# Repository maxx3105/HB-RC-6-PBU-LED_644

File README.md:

# HB-RC-6-PBU-LED_644
6-Fach Wandtaster mit Signal-Led auf Basis der AskSin++ für Homematic

Dieses Projekt basiert auf der Arbeit von [pa-pa](https://github.com/pa-pa/AskSinPP) ,[Jérôme](https://github.com/jp112sdl/Beispiel_AskSinPP).

# Hardware

### Bauteile

Bauteile                   | Bezeichnung          | Anzahl | Kommentar   | 
-------------------------- | -------------------- | ------ | ----------- | 
R1,R2                      | 240 Ohm              |   2    |             |
R3,R4                      | 10K Ohm              |   2    |             |
R5                         | 1K  Ohm              |   1    |             |
R6                         | 100K Ohm             |   1    |             |
C1, ..., C10               | 100n                 |   10   |             |
SW1, ..., SW7              | Taster               |   7    |             |
U1                         | Atmega 644P-AU       |   1    |             |
U2                         | CC1101               |   1    |             |
U3                         | SN74LVC1T45DBV       |   1    |             |
Q1                         | IRLML9301            |   1    |             |
D1                         | SMD Led 0805 Rot     |   1    |             |
D2                         | SMD Led 0805 Grün    |   1    |             |
D3,...,D8                  | SK6812 Mini          |   6    |             |
D9,...,D14                 | WS2812-2020          |   6    | Alternative |

Reichelt Liste comeing soon

#### Sonstiges

CC1101 https://de.aliexpress.com/item/32924239954.html

Taster https://de.aliexpress.com/item/32660690016.html?spm=a2g0s.9042311.0.0.27424c4dqj9wVN

~8,3 cm Draht als Antenne

### Programmieradapter

- 1x FTDI Programmer https://www.az-delivery.de/products/ftdi-adapter-ft232rl
- 1x ISP Programmer https://www.diamex.de/dxshop/USB-ISP-Programmer-fuer-Atmel-AVR

# Software

https://www.arduino.cc/en/software

### Firmware

Sketch https://github.com/jp112sdl/HB-RC-6-PBU-LED/blob/master/HB-RC-6-PBU-LED.ino

# Bauanleitung

coming soon

# Bilder

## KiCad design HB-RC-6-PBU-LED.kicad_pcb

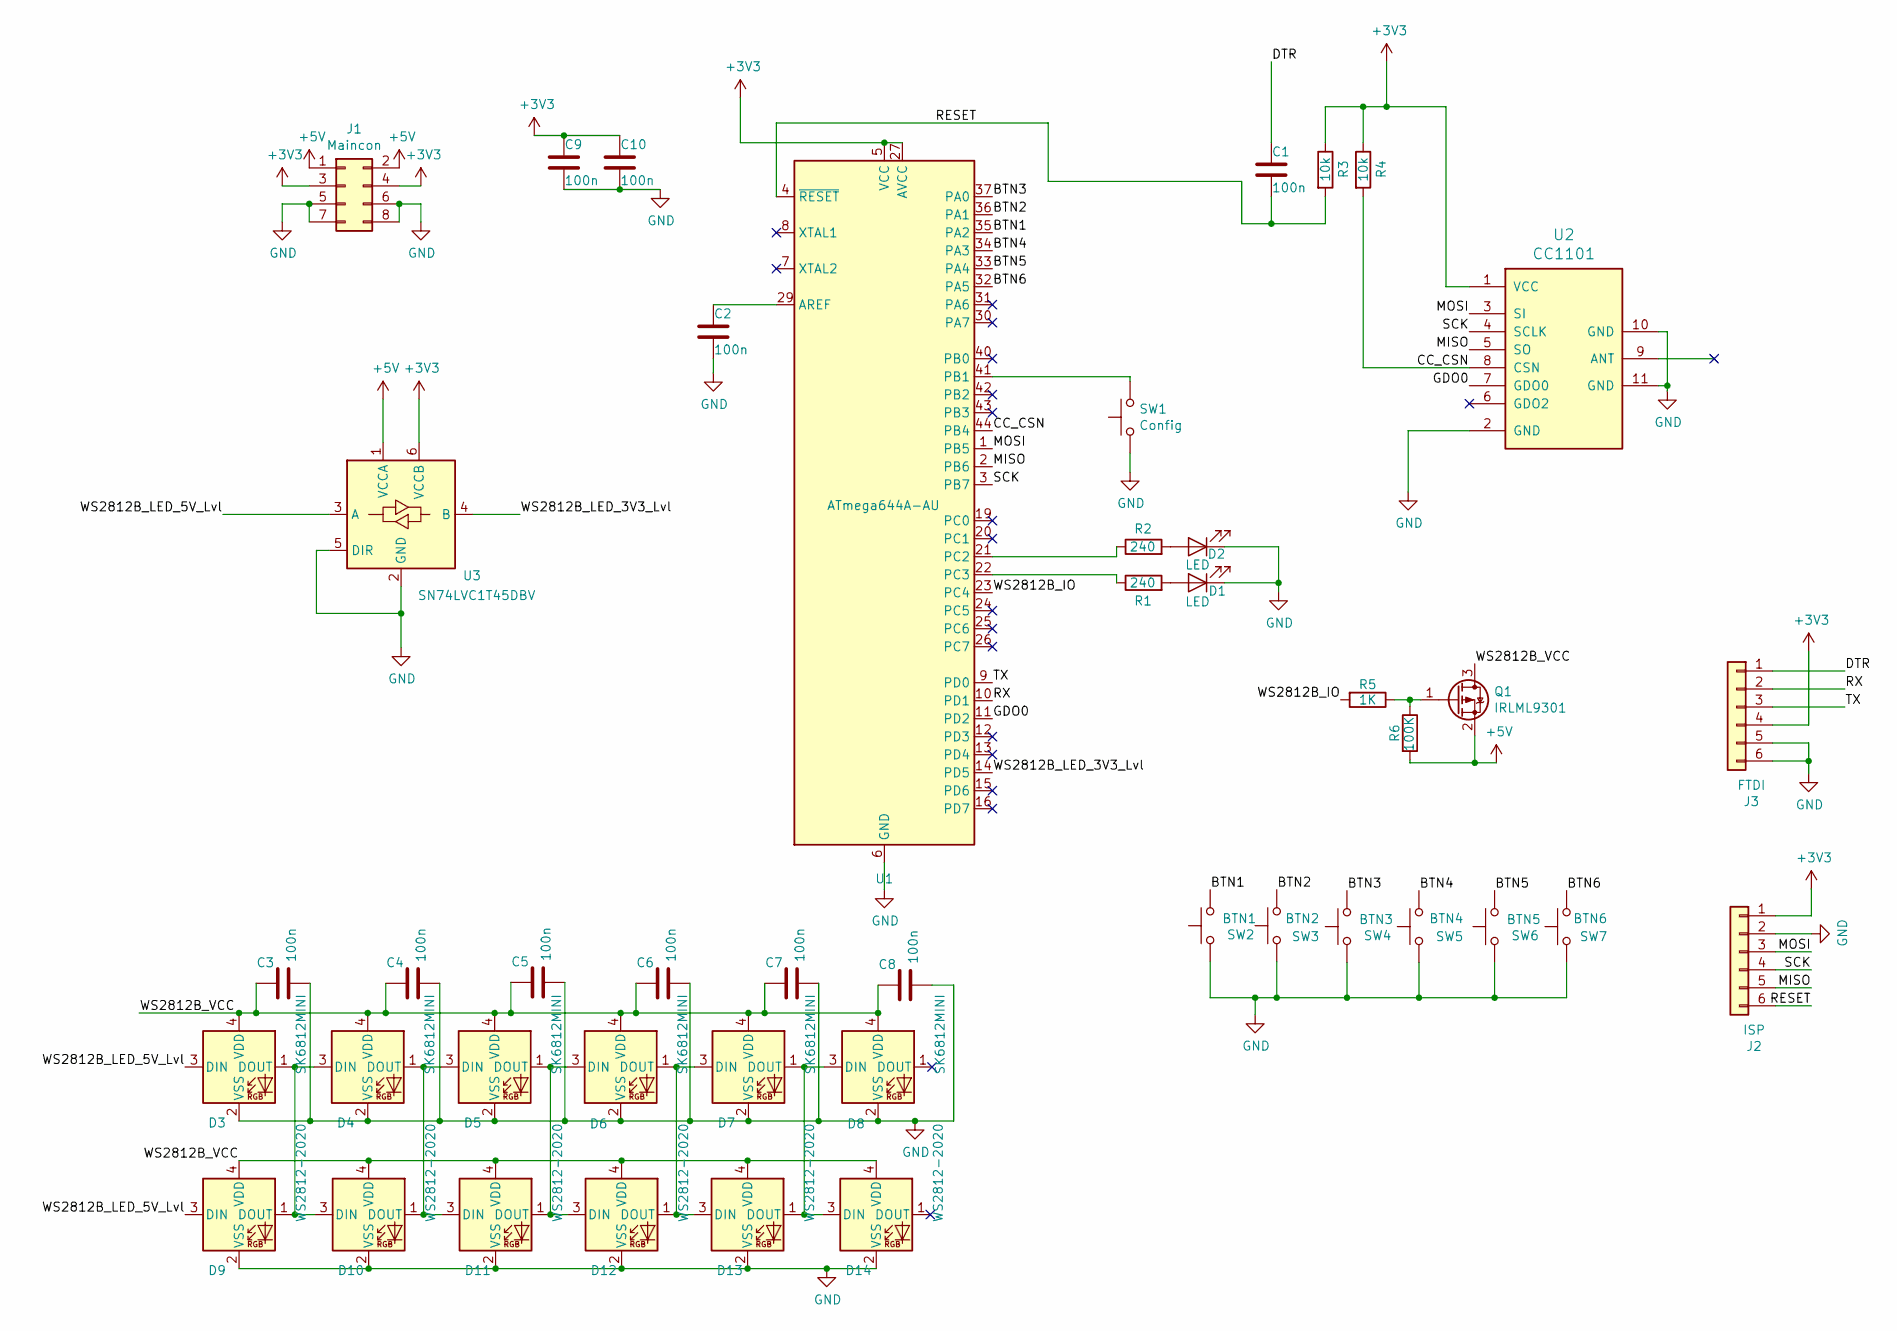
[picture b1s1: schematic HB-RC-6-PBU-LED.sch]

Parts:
C1, C2, C3, C4, C5, C6, C7, C8, C9, C10: 100n; C_0805_2012Metric_Pad1.18x1.45mm_HandSolder
D1, D2: LED; LED_0805_2012Metric_Pad1.15x1.40mm_HandSolder
D3, D4, D5, D6, D7, D8: SK6812MINI; LED_SK6812MINI_PLCC4_3.5x3.5mm_P1.75mm
D9, D10, D11, D12, D13, D14: WS2812-2020; LED_WS2812-2020
J1: Maincon; PinHeader_2x04_P2.54mm_Vertical_SMD
J2: ISP; PinHeader_1x06_P2.54mm_Vertical
J3: FTDI; PinHeader_1x06_P2.54mm_Vertical
Q1: IRLML9301; SOT-23
R1, R2: 240; R_0805_2012Metric_Pad1.20x1.40mm_HandSolder
R3, R4: 10k; R_0805_2012Metric_Pad1.20x1.40mm_HandSolder
R5: 1K; R_0805_2012Metric_Pad1.20x1.40mm_HandSolder
R6: 100K; R_0805_2012Metric_Pad1.20x1.40mm_HandSolder
SW1: Config; SW_SPST_FSMSM
SW2: BTN1; SW_SPST_FSMSM
SW3: BTN2; SW_SPST_FSMSM
SW4: BTN3; SW_SPST_FSMSM
SW5: BTN4; SW_SPST_FSMSM
SW6: BTN5; SW_SPST_FSMSM
SW7: BTN6; SW_SPST_FSMSM
U1: ATmega644A-AU; TQFP-44_10x10mm_P0.8mm
U2: CC1101; CC1101_SMD_THT
U3: SN74LVC1T45DBV; SOT-23-6

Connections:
+3V3: C9.1, C10.1, J1.3, J1.4, J2.1, J3.4, R3.1, R4.1, U1.5 (VCC), U1.17 (VCC), U1.27 (AVCC), U1.38 (VCC), U2.1 (VCC), U3.6 (VCCB)
+5V: J1.1, J1.2, Q1.2 (S), R6.2, U3.1 (VCCA)
/BTN1: SW2.2, U1.35 (PA2)
/BTN2: SW3.2, U1.36 (PA1)
/BTN3: SW4.2, U1.37 (PA0)
/BTN4: SW5.2, U1.34 (PA3)
/BTN5: SW6.2, U1.33 (PA4)
/BTN6: SW7.2, U1.32 (PA5)
/CC_CSN: R4.2, U1.44 (PB4), U2.8 (CSN)
/DTR: C1.1, J3.1
/GDO0: U1.11 (PD2), U2.7 (GDO0)
/MISO: J2.5, U1.2 (PB6), U2.5 (SO)
/MOSI: J2.3, U1.1 (PB5), U2.3 (SI)
/RESET: C1.2, J2.6, R3.2, U1.4 (~RESET)
/RX: J3.2, U1.10 (PD1)
/SCK: J2.4, U1.3 (PB7), U2.4 (SCLK)
/TX: J3.3, U1.9 (PD0)
/WS2812B_IO: R5.2, U1.23 (PC4)
/WS2812B_LED_3V3_Lvl: U1.14 (PD5), U3.4 (B)
/WS2812B_LED_5V_Lvl: D3.3 (DIN), D9.3 (DIN), U3.3 (A)
/WS2812B_VCC: C3.2, C4.2, C5.2, C6.2, C7.2, C8.2, D3.4 (VDD), D4.4 (VDD), D5.4 (VDD), D6.4 (VDD), D7.4 (VDD), D8.4 (VDD), D9.4 (VDD), D10.4 (VDD), D11.4 (VDD), D12.4 (VDD), D13.4 (VDD), D14.4 (VDD), Q1.3 (D)
GND: C2.2, C3.1, C4.1, C5.1, C6.1, C7.1, C8.1, C9.2, C10.2, D1.1 (K), D2.1 (K), D3.2 (VSS), D4.2 (VSS), D5.2 (VSS), D6.2 (VSS), D7.2 (VSS), D8.2 (VSS), D9.2 (VSS), D10.2 (VSS), D11.2 (VSS), D12.2 (VSS), D13.2 (VSS), D14.2 (VSS), J1.5, J1.6, J1.7, J1.8, J2.2, J3.5, J3.6, SW1.1, SW2.1, SW3.1, SW4.1, SW5.1, SW6.1, SW7.1, U1.6 (GND), U1.18 (GND), U1.28 (GND), U1.39 (GND), U2.2 (GND), U2.10 (GND), U2.11 (GND), U3.2 (GND), U3.5 (DIR)
unnamed: C2.1, U1.29 (AREF)
unnamed: D1.2 (A), R1.2
unnamed: D2.2 (A), R2.2
unnamed: D4.1 (DOUT), D5.3 (DIN), D10.1 (DOUT), D11.3 (DIN)
unnamed: D3.1 (DOUT), D4.3 (DIN), D9.1 (DOUT), D10.3 (DIN)
unnamed: D5.1 (DOUT), D6.3 (DIN), D11.1 (DOUT), D12.3 (DIN)
unnamed: D6.1 (DOUT), D7.3 (DIN), D12.1 (DOUT), D13.3 (DIN)
unnamed: D7.1 (DOUT), D8.3 (DIN), D13.1 (DOUT), D14.3 (DIN)
unnamed: Q1.1 (G), R5.1, R6.1
unnamed: R1.1, U1.22 (PC3)
unnamed: R2.1, U1.21 (PC2)
unnamed: SW1.2, U1.41 (PB1)

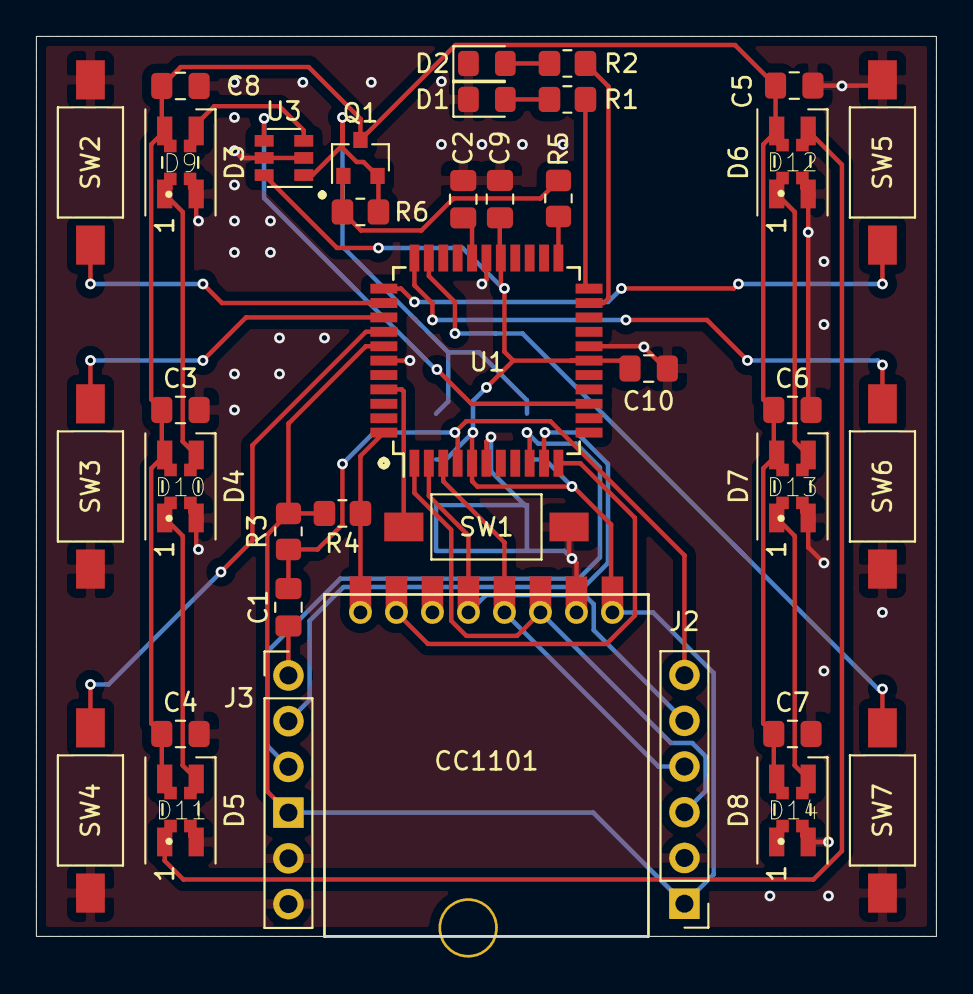
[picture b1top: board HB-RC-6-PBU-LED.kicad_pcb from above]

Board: 2 copper layers, 50.0 x 50.0 mm, 44 parts (1 on the bottom side), 34 nets.

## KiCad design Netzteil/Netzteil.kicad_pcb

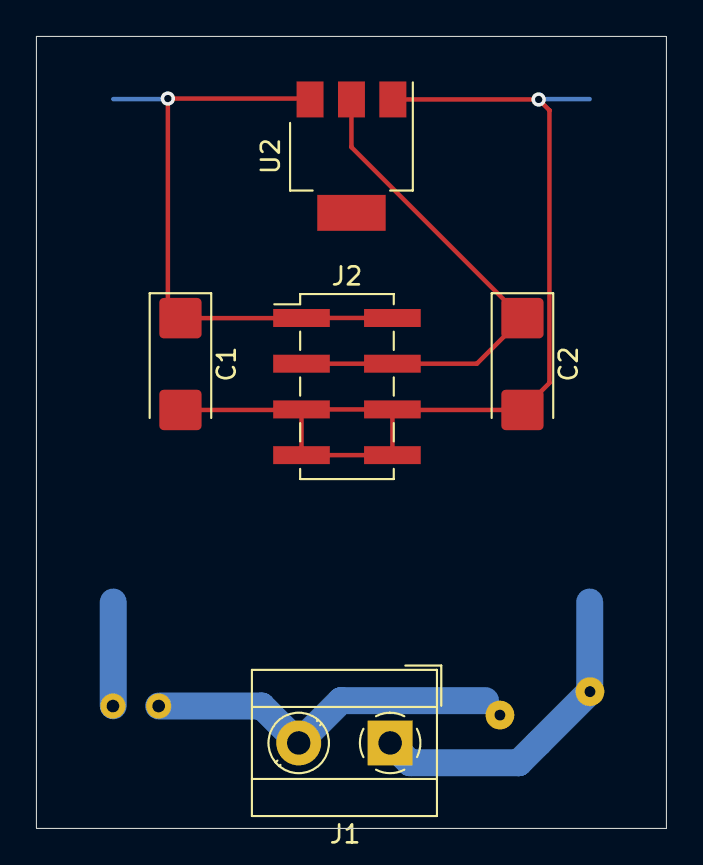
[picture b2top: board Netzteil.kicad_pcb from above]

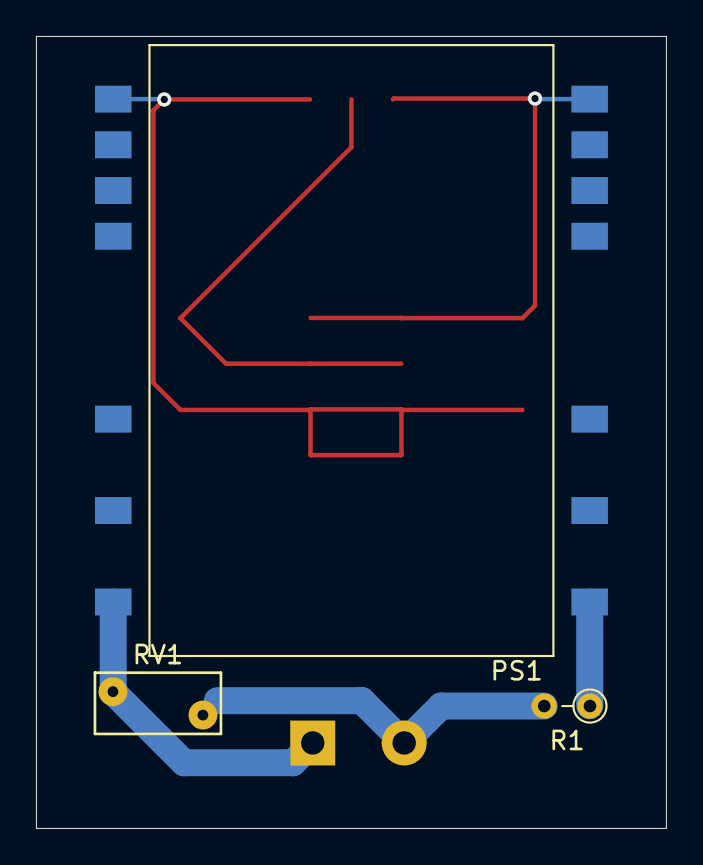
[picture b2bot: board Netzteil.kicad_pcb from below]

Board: 2 copper layers, 35.0 x 44.0 mm, 8 parts (3 on the bottom side), 6 nets.

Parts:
C1, C2: 10µ; CP_EIA-6032-28_Kemet-C_Pad2.25x2.35mm_HandSolder
J1: Screw_Terminal_01x02; TerminalBlock_MetzConnect_Type101_RT01602HBWC_1x02_P5.08mm_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
J2: Conn_02x04_Odd_Even; PinHeader_2x04_P2.54mm_Vertical_SMD
PS1: IRM-02-5S; Converter_ACDC_MeanWell_IRM-02-xx_SMD
R1: 1K; R_Axial_DIN0204_L3.6mm_D1.6mm_P2.54mm_Vertical
RV1: Varistor; RV_Disc_D7mm_W3.4mm_P5mm
U2: TLV1117-33; SOT-223

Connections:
+3V3: C2.1, J2.3, J2.4, U2.2
+5V: C1.1, J2.1, J2.2, PS1.12, U2.3
GND: C1.2, C2.2, J2.5, J2.6, J2.7, J2.8, PS1.13, U2.1
unnamed: J1.1, PS1.24, RV1.2
unnamed: J1.2, R1.2, RV1.1
unnamed: PS1.1, R1.1

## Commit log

2021-05-09 Bugfix
2021-05-22 Add files via upload
    bugfix
2021-06-07 Bugfix on Transceiver PIN A B
